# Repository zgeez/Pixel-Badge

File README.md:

# Pixel Badge

A wearable 32 × 32 LED badge that shows a QR code, text and animations, and
hands out a contact link over NFC. A phone app sets it up over Bluetooth.

I designed the PCB in KiCad, wrote the firmware on Zephyr, and built the
Android app in Flutter. The firmware started on an nRF5340 DK with a HUB75
panel and now runs on the custom nRF52840 board.

## Where it stands

Rev A boards are built and working (November 2026). Bring-up turned up an
assembly fault on the module, a scan that flickered, and a few USB and
charging quirks. All are fixed. Board 1 runs everything: display, BLE, NFC,
motion, audio and charging. It lasted 22 hours on the battery showing a QR
code at half brightness.

Bare LEDs make a QR code that phones struggle to read. A printed white diffuser
over the matrix fixes that, so the code scans easily. That's a first hands-on
result, not a formal scan test yet.

Still untested: NFC and BLE range, thermals, and System OFF on the battery.
[Bring-up record](validation/results/2026-11-03-rev-a-bringup/README.md),
[all test records](docs/validation.md).

<p align="center">
  
  <br>
  <em>Tilt-driven particle fluid (click for video).</em>
</p>

## What it does

- Shows a contact QR code and serves the same link from a passive NFC tag.
- Displays text, drawings and grayscale animations of up to 128 frames.
- Rotates with the IMU and runs a particle fluid effect.
- Shows microphone level and spectrum. An opt-in bench build can stream
  encrypted audio to the phone, which stores it. Audio never touches the
  badge's flash.

## Inside

| | |
|---|---|
| MCU | Ebyte E73 module (nRF52840), BLE and app on one core |
| Display | 1024 white LEDs at 2 mm pitch, constant-current column drivers, hardware-timed scan |
| Board | 118 × 76 mm, four layers, all parts on the front |
| Power | USB-C, BQ25620 charger, protected 2500 mAh LiPo, separate LED rail |
| Sensors | ICM-42688-P IMU, PDM microphone, NT3H2111 NFC tag with a PCB coil |
| Firmware | C++17 and C on Zephyr, nRF Connect SDK 3.4.1 |
| App | Flutter, Android |

The CPU doesn't drive the LED scan. SPI DMA, timers and PPI do, and the CPU
takes one interrupt per brightness plane. If the firmware ever stops, a
hardware one-shot blanks the matrix within about a millisecond. Settings
changes over BLE are staged, applied one at a time and read back before the
app shows them as done. [How it fits together](docs/architecture.md).

## Carrier

A 3D-printed carrier holds the board and battery. It clips on with a magnetic
backing or hangs from a lanyard, in portrait or landscape. Print files are in
[hardware/mechanical](hardware/mechanical/).

## Prototype

Before the boards existed, the firmware ran on an nRF5340 DK driving an RGB
HUB75 panel, with breakout boards for the tag, IMU and microphone. That bench
still builds and is useful for app work.

## App

Badge, Links, Text and Studio pages (test data). [App README](app/README.md).

## Build

Install nRF Connect SDK 3.4.1 and its toolchain, then from PowerShell:

```powershell
.\scripts\dev.ps1 build -Image Main -Pristine
.\scripts\dev.ps1 build -Image Prototype -Pristine
.\scripts\dev.ps1 test     # host tests, needs Docker
.\scripts\dev.ps1 check
```

Main ships with the LED output, charging and recording turned off. Bench
add-ons turn them on deliberately. [Firmware guide](docs/firmware.md),
[bring-up checklist](docs/bringup.md).

## Repository

[firmware/](firmware/README.md), [hardware/](hardware/README.md),
[app/](app/README.md), [docs/](docs/README.md),
[design decisions](docs/decisions/README.md).

## License

[MIT](LICENSE), with some [third-party notices and Apache-2.0 board files](docs/firmware.md#licenses).

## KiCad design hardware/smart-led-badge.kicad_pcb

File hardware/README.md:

# Hardware

The KiCad 10.0.6 project for the Rev A badge: a 118 × 76 mm, four-layer board
with every assembled part on the front. Boards are built and running
([bring-up record](../validation/results/2026-11-03-rev-a-bringup/README.md)).

Open `smart-led-badge.kicad_pro`. Project libraries use `${KIPRJMOD}` paths,
and you'll also need KiCad's standard libraries.

| Path | Contents |
|---|---|
| `smart-led-badge.kicad_sch`, `sheets/` | Schematic |
| `smart-led-badge.kicad_pcb` | Routed board |
| `smart-led-badge.kicad_dru` | Custom design rules |
| [libraries/](libraries/README.md) | Symbols, footprints and where they came from |
| `mechanical/` | 3MF print files, below |

## Board

- 1.6 mm, 3 mm corner radius, JLC04161H-7628 stack-up, tented vias.
- Rows route on F.Cu and columns via to In2.Cu. In1.Cu is ground apart from
  three short links.
- 0.127 mm minimum track and space, 0.45/0.2 mm vias. The custom rules allow
  the matrix LEDs' courtyards to touch.
- Keep-outs for the NFC coil, the antenna and the battery. Nothing is
  assembled or exposed under the pack.
- Test points, battery polarity and controls are labelled on silkscreen.
  Reference designators aren't printed.

## Print files

| File | Part |
|---|---|
| `rear-carrier.3mf`, `front-face.3mf` | The two halves of the carrier |
| `matrix-pixel-grid.3mf`, `matrix-diffuser.3mf` | Black 2 mm grid and white diffuser over the matrix |
| `mode-button-cap.3mf`, `action-button-cap.3mf`, `button-plunger.3mf` | Button parts |
| `magnetic-backing.3mf`, `magnet-retaining-cap.3mf` | Magnetic mount |
| `m2-thread-coupon.3mf` | Test print for the M2 threads |
| `pcb-no-rear-jst.3mf` | Board dummy for fit checks (without the rear connector) |

The diffuser is what makes the QR code readable for phones. Fit, latch
retention and wear still need checking on prints.

## Checks

```powershell
.\scripts\dev.ps1 hardware
```

On Linux, `make hardware`. It runs ERC, checks that symbol pin numbers match
footprint pads, and exports PDF and BOM files to `build/hardware/`. It
doesn't check footprint geometry or pin functions, and DRC is separate.
Gerbers, drill, placement and STEP files are generated and kept out of the
repository.

[Hardware overview](../docs/hardware.md), [bring-up checklist](../docs/bringup.md).

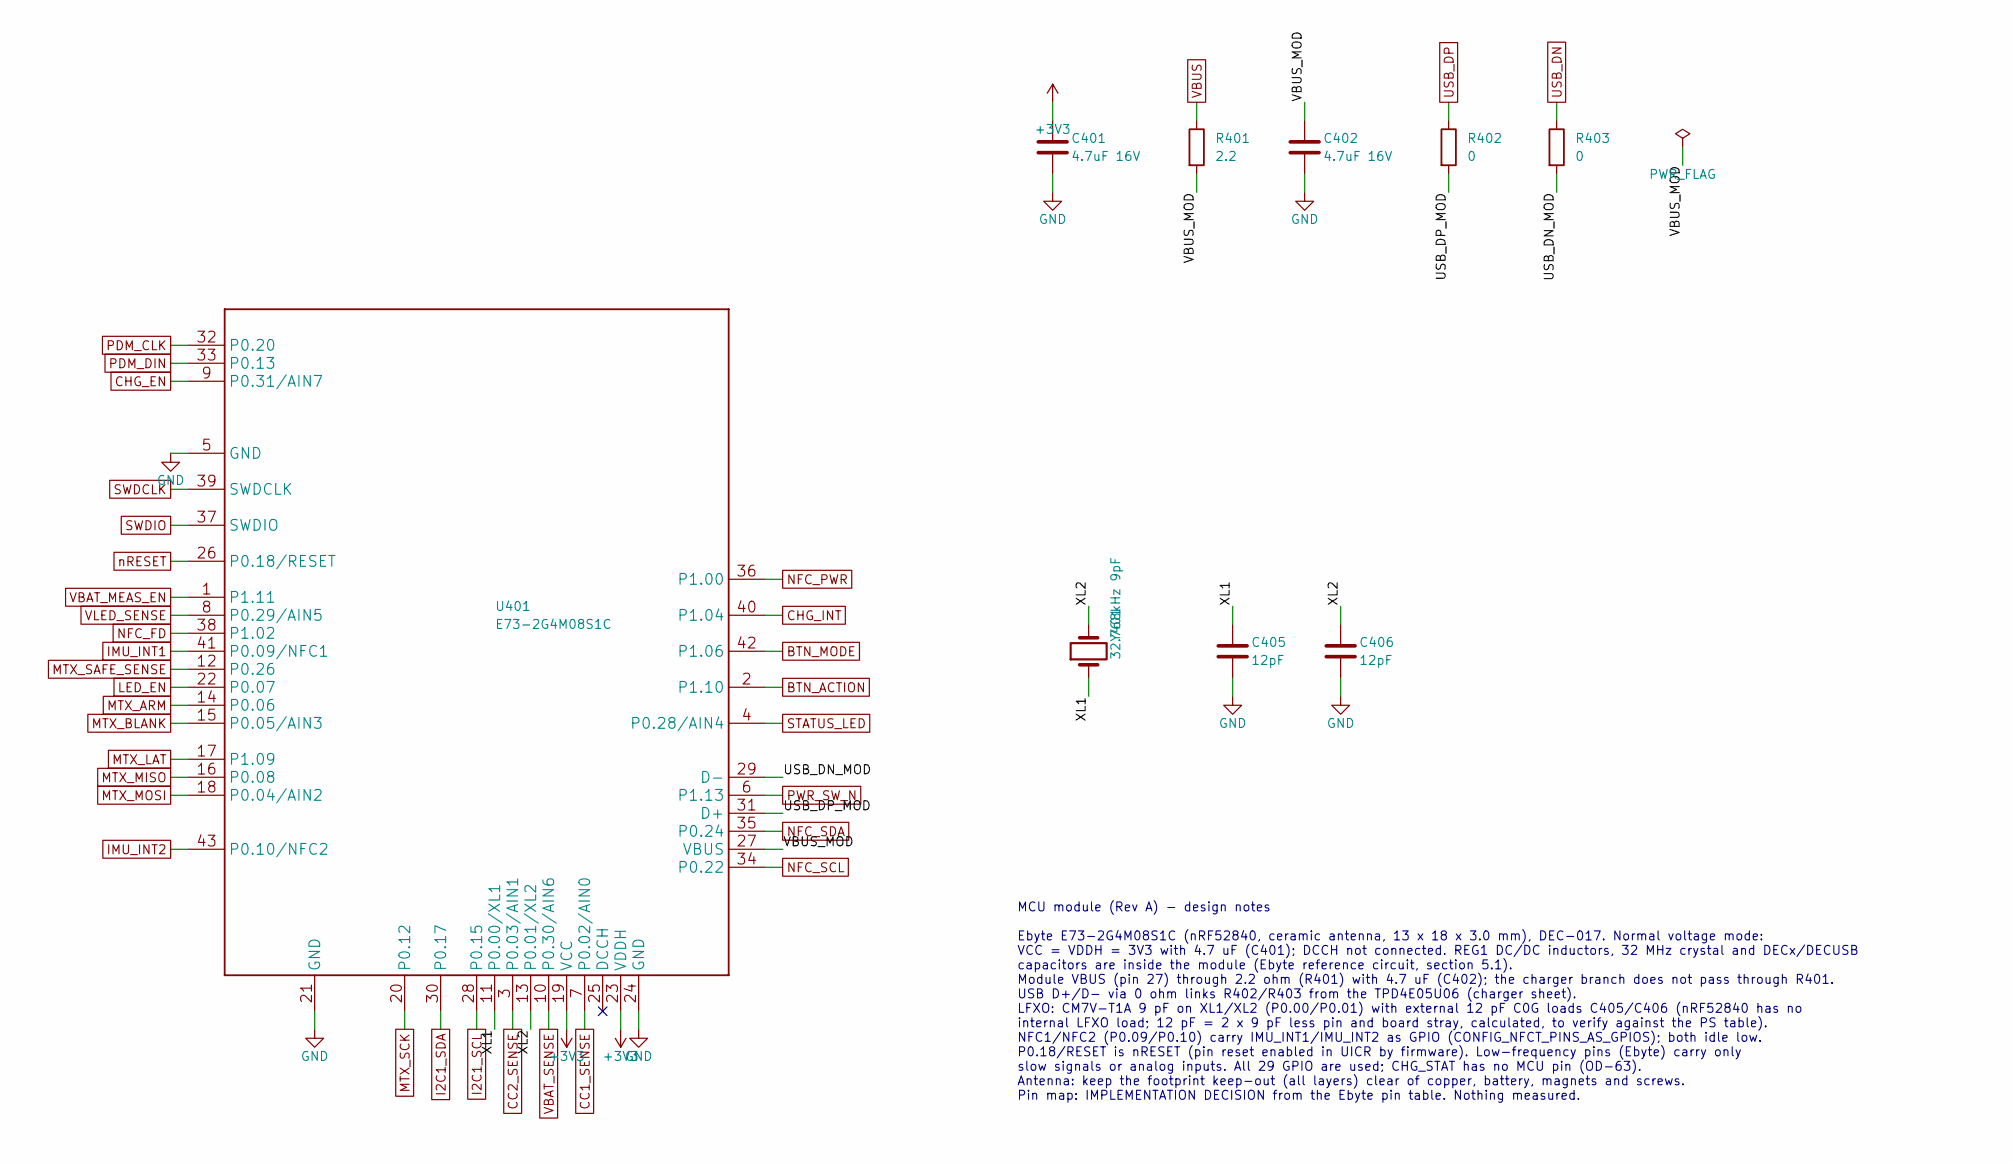
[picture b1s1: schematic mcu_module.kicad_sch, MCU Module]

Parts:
C401, C402: 4.7uF 16V; C_0603_1608Metric; MPN CL10A475KO8NNNC; LCSC C19666
C405, C406: 12pF; C_0402_1005Metric; MPN 0402CG120J500NT; LCSC C1547
R401: 2.2; R_0603_1608Metric; MPN 0603WAF220KT5E; LCSC C22939
R402, R403: 0; R_0402_1005Metric; MPN 0402WGF0000TCE; LCSC C17168
U401: E73-2G4M08S1C; Ebyte_E73-2G4M08S1C; MPN E73-2G4M08S1C; LCSC C356849
Y401: 32.768kHz 9pF; Crystal_SMD_3215-2Pin_3.2x1.5mm; MPN CM7V-T1A-32.768KHZ-9PF-20PPM-TA-QC; LCSC C5366538

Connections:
+3V3: C401.1, U401.19 (VCC), U401.23 (VDDH); also elsewhere on the board
/MCU Module/USB_DN_MOD: R403.2, U401.29 (D-)
/MCU Module/USB_DP_MOD: R402.2, U401.31 (D+)
/MCU Module/VBUS_MOD: C402.1, R401.2, U401.27 (VBUS)
/MCU Module/XL1: C405.1, U401.11 (P0.00/XL1), Y401.1
/MCU Module/XL2: C406.1, U401.13 (P0.01/XL2), Y401.2
BTN_ACTION: U401.2 (P1.10); also elsewhere on the board
BTN_MODE: U401.42 (P1.06); also elsewhere on the board
CC1_SENSE: U401.7 (P0.02/AIN0); also elsewhere on the board
CC2_SENSE: U401.3 (P0.03/AIN1); also elsewhere on the board
CHG_EN: U401.9 (P0.31/AIN7); also elsewhere on the board
CHG_INT: U401.40 (P1.04); also elsewhere on the board
GND: C401.2, C402.2, C405.2, C406.2, U401.5 (GND), U401.21 (GND), U401.24 (GND); also elsewhere on the board
I2C1_SCL: U401.28 (P0.15); also elsewhere on the board
I2C1_SDA: U401.30 (P0.17); also elsewhere on the board
IMU_INT1: U401.41 (P0.09/NFC1); also elsewhere on the board
IMU_INT2: U401.43 (P0.10/NFC2); also elsewhere on the board
LED_EN: U401.22 (P0.07); also elsewhere on the board
MTX_ARM: U401.14 (P0.06); also elsewhere on the board
MTX_BLANK: U401.15 (P0.05/AIN3); also elsewhere on the board
MTX_LAT: U401.17 (P1.09); also elsewhere on the board
MTX_MISO: U401.16 (P0.08); also elsewhere on the board
MTX_MOSI: U401.18 (P0.04/AIN2); also elsewhere on the board
MTX_SAFE_SENSE: U401.12 (P0.26); also elsewhere on the board
MTX_SCK: U401.20 (P0.12); also elsewhere on the board
NFC_FD: U401.38 (P1.02); also elsewhere on the board
NFC_PWR: U401.36 (P1.00); also elsewhere on the board
NFC_SCL: U401.34 (P0.22); also elsewhere on the board
NFC_SDA: U401.35 (P0.24); also elsewhere on the board
PDM_CLK: U401.32 (P0.20); also elsewhere on the board
PDM_DIN: U401.33 (P0.13); also elsewhere on the board
PWR_SW_N: U401.6 (P1.13); also elsewhere on the board
STATUS_LED: U401.4 (P0.28/AIN4); also elsewhere on the board
SWDCLK: U401.39 (SWDCLK); also elsewhere on the board
SWDIO: U401.37 (SWDIO); also elsewhere on the board
USB_DN: R403.1; also elsewhere on the board
USB_DP: R402.1; also elsewhere on the board
VBAT_MEAS_EN: U401.1 (P1.11); also elsewhere on the board
VBAT_SENSE: U401.10 (P0.30/AIN6); also elsewhere on the board
VBUS: R401.1; also elsewhere on the board
VLED_SENSE: U401.8 (P0.29/AIN5); also elsewhere on the board
nRESET: U401.26 (P0.18/RESET); also elsewhere on the board

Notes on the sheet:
MCU module (Rev A) - design notes Ebyte E73-2G4M08S1C (nRF52840, ceramic antenna, 13 x 18 x 3.0 mm), DEC-017. Normal voltage mode: VCC = VDDH = 3V3 with 4.7 uF (C401); DCCH not connected. REG1 DC/DC inductors, 32 MHz crystal and DECx/DECUSB capacitors are inside the module (Ebyte reference circuit,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

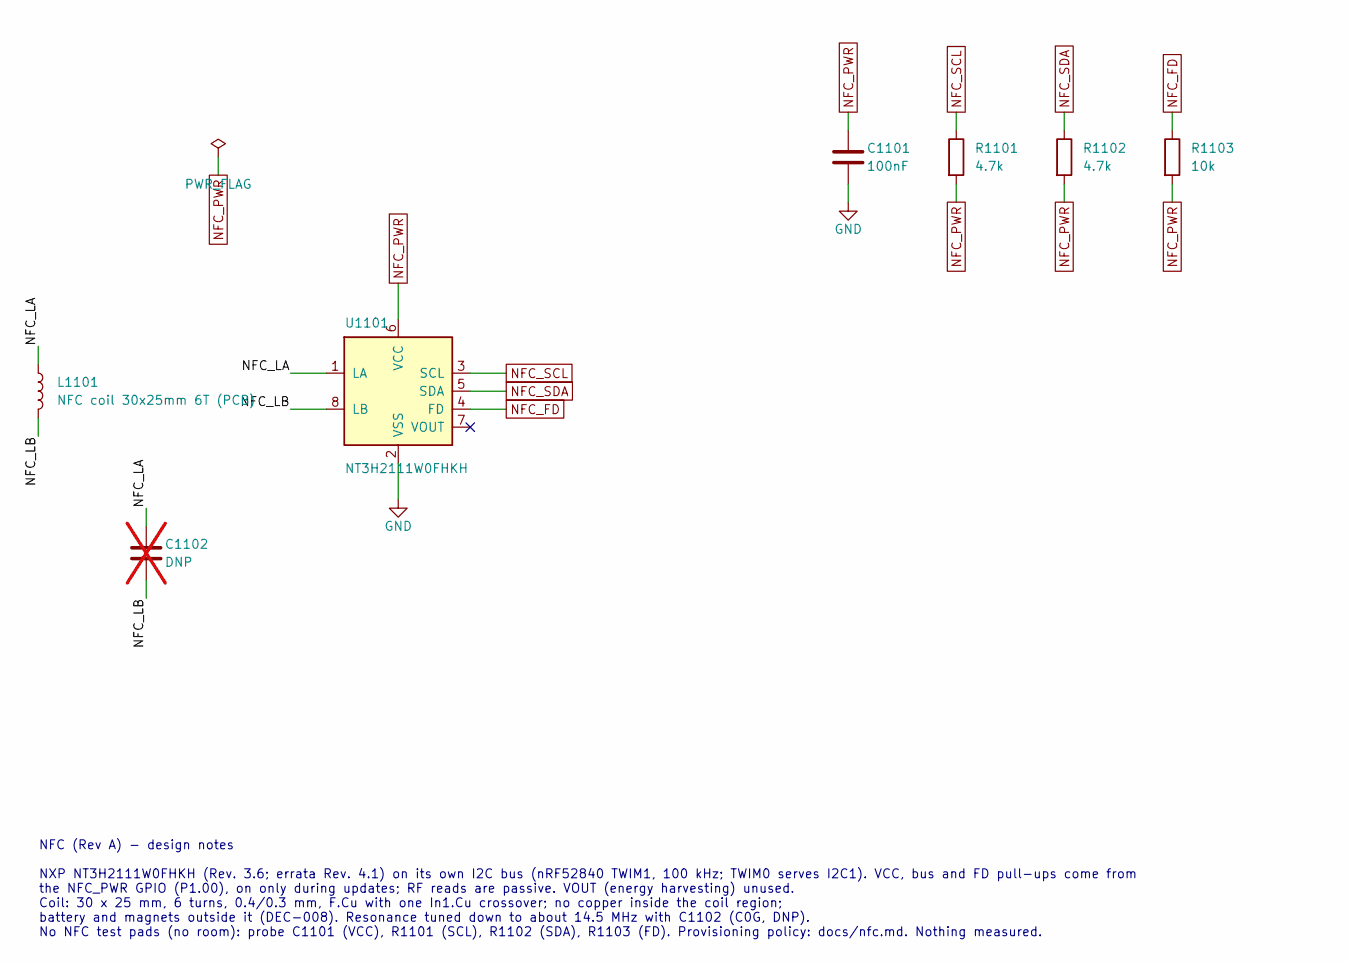
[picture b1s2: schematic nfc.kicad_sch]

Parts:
C1101: 100nF; C_0402_1005Metric; MPN CL05B104KO5NNNC; LCSC C1525
C1102: DNP; C_0402_1005Metric; not fitted
L1101: NFC coil 30x25mm 6T (PCB); L_NFC_Coil_30x25mm_6T
R1101, R1102: 4.7k; R_0402_1005Metric; MPN 0402WGF4701TCE; LCSC C25900
R1103: 10k; R_0402_1005Metric; MPN 0402WGF1002TCE; LCSC C25744
U1101: NT3H2111W0FHKH; NXP_XQFN-8_SOT902-3; MPN NT3H2111W0FHKH; LCSC C710403

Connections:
/NFC/NFC_LA: C1102.1, L1101.1, U1101.1 (LA)
/NFC/NFC_LB: C1102.2, L1101.2, U1101.8 (LB)
GND: C1101.2, U1101.2 (VSS); also elsewhere on the board
NFC_FD: R1103.1, U1101.4 (FD); also elsewhere on the board
NFC_PWR: C1101.1, R1101.2, R1102.2, R1103.2, U1101.6 (VCC); also elsewhere on the board
NFC_SCL: R1101.1, U1101.3 (SCL); also elsewhere on the board
NFC_SDA: R1102.1, U1101.5 (SDA); also elsewhere on the board

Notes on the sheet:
NFC (Rev A) - design notes NXP NT3H2111W0FHKH (Rev. 3.6; errata Rev. 4.1) on its own I2C bus (nRF52840 TWIM1, 100 kHz; TWIM0 serves I2C1). VCC, bus and FD pull-ups come from the NFC_PWR GPIO (P1.00), on only during updates; RF reads are passive. VOUT (energy harvesting) unused. Coil: 30 x 25 mm, 6 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

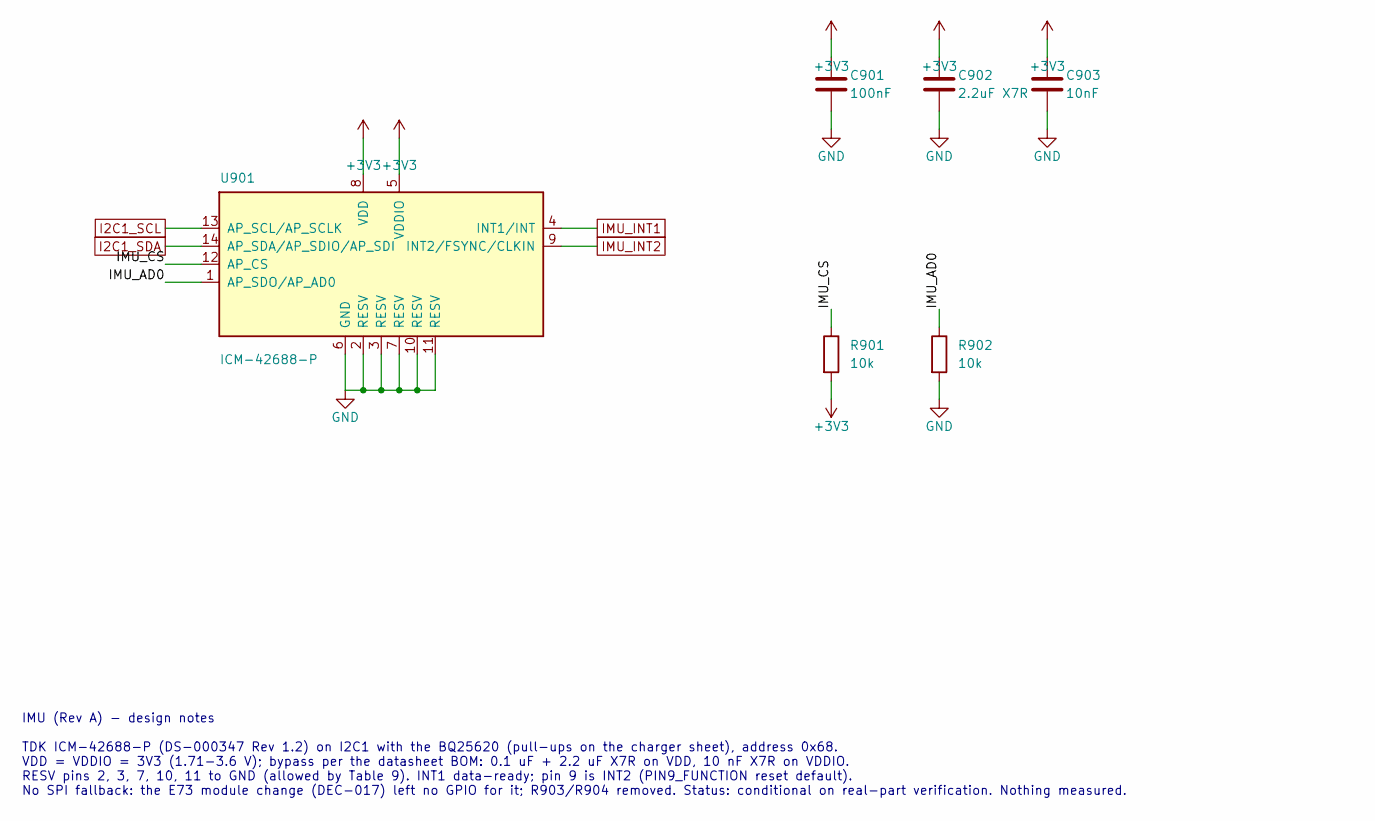
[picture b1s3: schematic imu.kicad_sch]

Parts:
C901: 100nF; C_0402_1005Metric; MPN CL05B104KO5NNNC; LCSC C1525
C902: 2.2uF X7R; C_0603_1608Metric; MPN 0603B225K160NT; LCSC C43922
C903: 10nF; C_0402_1005Metric; MPN CL05B103KB5NNNC; LCSC C15195
R901, R902: 10k; R_0402_1005Metric; MPN 0402WGF1002TCE; LCSC C25744
U901: ICM-42688-P; LGA-14_3x2.5mm_P0.5mm_LayoutBorder3x4y; MPN ICM-42688-P; LCSC C1850418

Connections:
+3V3: C901.1, C902.1, C903.1, R901.2, U901.5 (VDDIO), U901.8 (VDD); also elsewhere on the board
/IMU/IMU_AD0: R902.1, U901.1 (AP_SDO/AP_AD0)
/IMU/IMU_CS: R901.1, U901.12 (AP_CS)
GND: C901.2, C902.2, C903.2, R902.2, U901.2 (RESV), U901.3 (RESV), U901.6 (GND), U901.7 (RESV), U901.10 (RESV), U901.11 (RESV); also elsewhere on the board
I2C1_SCL: U901.13 (AP_SCL/AP_SCLK); also elsewhere on the board
I2C1_SDA: U901.14 (AP_SDA/AP_SDIO/AP_SDI); also elsewhere on the board
IMU_INT1: U901.4 (INT1/INT); also elsewhere on the board
IMU_INT2: U901.9 (INT2/FSYNC/CLKIN); also elsewhere on the board

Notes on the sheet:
IMU (Rev A) - design notes TDK ICM-42688-P (DS-000347 Rev 1.2) on I2C1 with the BQ25620 (pull-ups on the charger sheet), address 0x68. VDD = VDDIO = 3V3 (1.71-3.6 V); bypass per the datasheet BOM: 0.1 uF + 2.2 uF X7R on VDD, 10 nF X7R on VDDIO. RESV pins 2, 3, 7, 10, 11 to GND (allowed by Table 9).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

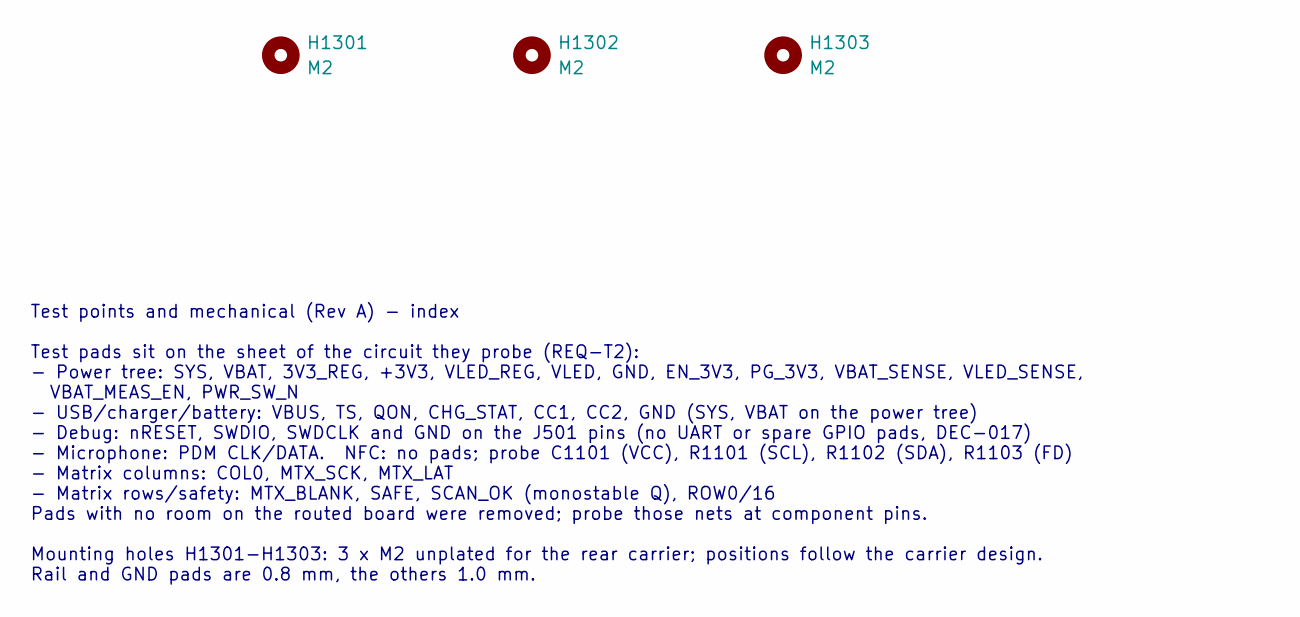
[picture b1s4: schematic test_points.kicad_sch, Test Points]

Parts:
H1301, H1302, H1303: M2; MountingHole_2.2mm_M2

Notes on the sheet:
Test points and mechanical (Rev A) - index Test pads sit on the sheet of the circuit they probe (REQ-T2): - Power tree: SYS, VBAT, 3V3_REG, +3V3, VLED_REG, VLED, GND, EN_3V3, PG_3V3, VBAT_SENSE, VLED_SENSE, VBAT_MEAS_EN, PWR_SW_N - USB/charger/battery: VBUS, TS, QON, CHG_STAT, CC1, CC2, GND (SYS, V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

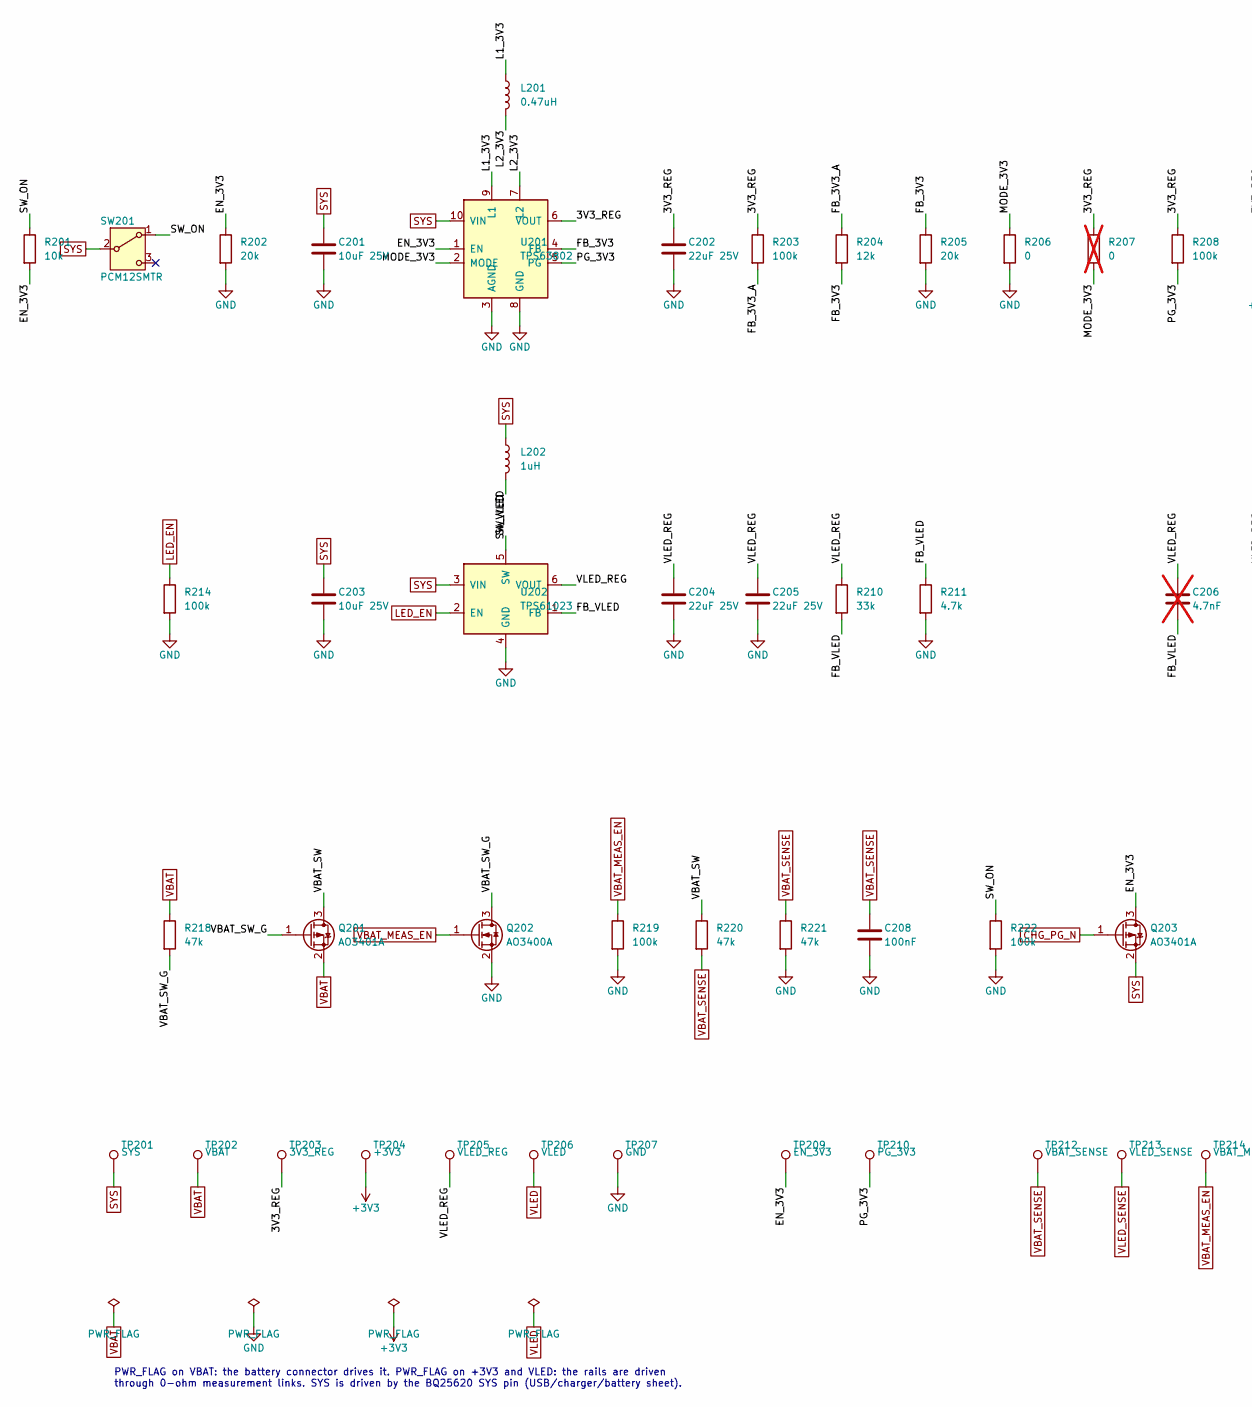
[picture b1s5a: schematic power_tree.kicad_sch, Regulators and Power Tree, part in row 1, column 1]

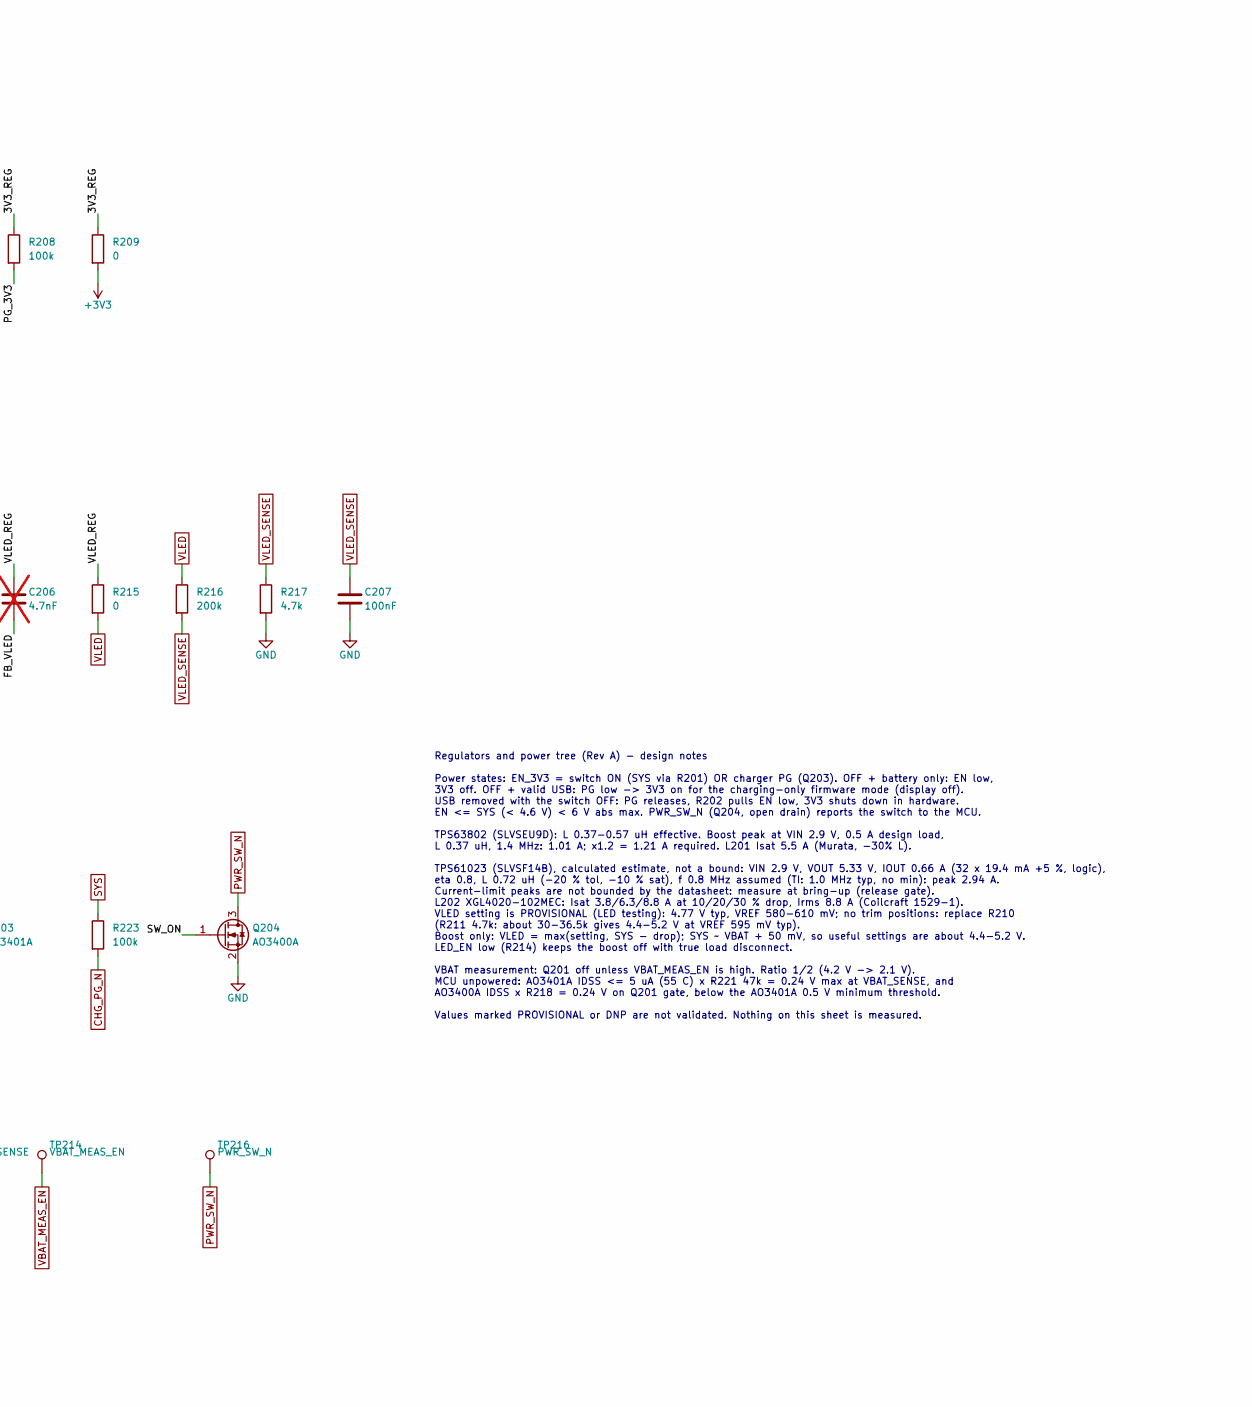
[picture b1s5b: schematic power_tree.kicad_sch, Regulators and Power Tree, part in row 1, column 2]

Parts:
C201, C203: 10uF 25V; C_0805_2012Metric; MPN CL21A106KAYNNNE; LCSC C15850
C202, C204, C205: 22uF 25V; C_0805_2012Metric; MPN CL21A226MAQNNNE; LCSC C45783
C206: 4.7nF; C_0402_1005Metric; not fitted
C207, C208: 100nF; C_0402_1005Metric; MPN CL05B104KO5NNNC; LCSC C1525
L201: 0.47uH; L_Murata_DFE201612E; MPN DFE201612E-R47M=P2; LCSC C668312
L202: 1uH; L_Coilcraft_XGL4020; MPN XGL4020-102MEC; LCSC C5357696
Q201, Q203: AO3401A; SOT-23; MPN AO3401A; LCSC C15127
Q202, Q204: AO3400A; SOT-23; MPN AO3400A; LCSC C20917
R201: 10k; R_0402_1005Metric; MPN 0402WGF1002TCE; LCSC C25744
R202, R205: 20k; R_0402_1005Metric; MPN 0402WGF2002TCE; LCSC C25765
R203, R208, R214, R219, R222, R223: 100k; R_0402_1005Metric; MPN 0402WGF1003TCE; LCSC C25741
R204: 12k; R_0402_1005Metric; MPN 0402WGF1202TCE; LCSC C25752
R206: 0; R_0402_1005Metric; MPN 0402WGF0000TCE; LCSC C17168
R207: 0; R_0402_1005Metric; not fitted
R209, R215: 0; R_0805_2012Metric; MPN 0805W8F0000T5E; LCSC C17477
R210: 33k; R_0402_1005Metric; MPN 0402WGF3302TCE; LCSC C25779
R211, R217: 4.7k; R_0402_1005Metric; MPN 0402WGF4701TCE; LCSC C25900
R216: 200k; R_0402_1005Metric; MPN 0402WGF2003TCE; LCSC C25764
R218, R220, R221: 47k; R_0402_1005Metric; MPN 0402WGF4702TCE; LCSC C25792
SW201: PCM12SMTR; SW_SPDT_PCM12; MPN PCM12SMTR; LCSC C221841
TP201: SYS; TestPoint_Pad_D0.8mm
TP202: VBAT; TestPoint_Pad_D0.8mm
TP203: 3V3_REG; TestPoint_Pad_D0.8mm
TP204: +3V3; TestPoint_Pad_D0.8mm
TP205: VLED_REG; TestPoint_Pad_D0.8mm
TP206: VLED; TestPoint_Pad_D0.8mm
TP207: GND; TestPoint_Pad_D0.8mm
TP209: EN_3V3; TestPoint_Pad_D1.0mm
TP210: PG_3V3; TestPoint_Pad_D1.0mm
TP212: VBAT_SENSE; TestPoint_Pad_D1.0mm
TP213: VLED_SENSE; TestPoint_Pad_D1.0mm
TP214: VBAT_MEAS_EN; TestPoint_Pad_D1.0mm
TP216: PWR_SW_N; TestPoint_Pad_D1.0mm
U201: TPS63802; Texas_DLA0010A; MPN TPS63802DLAR; LCSC C2845237
U202: TPS61023; Texas_DRL0006A; MPN TPS61023DRLR; LCSC C919459

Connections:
+3V3: R209.2, TP204.1; also elsewhere on the board
/Regulators and Power Tree/3V3_REG: C202.1, R203.1, R207.1, R208.1, R209.1, TP203.1, U201.6 (VOUT)
/Regulators and Power Tree/EN_3V3: Q203.3 (D), R201.2, R202.1, TP209.1, U201.1 (EN)
/Regulators and Power Tree/FB_3V3: R204.2, R205.1, U201.4 (FB)
/Regulators and Power Tree/FB_3V3_A: R203.2, R204.1
/Regulators and Power Tree/FB_VLED: C206.2, R210.2, R211.1, U202.1 (FB)
/Regulators and Power Tree/L1_3V3: L201.1, U201.9 (L1)
/Regulators and Power Tree/L2_3V3: L201.2, U201.7 (L2)
/Regulators and Power Tree/MODE_3V3: R206.1, R207.2, U201.2 (MODE)
/Regulators and Power Tree/PG_3V3: R208.2, TP210.1, U201.5 (PG)
/Regulators and Power Tree/SW_ON: Q204.1 (G), R201.1, R222.1, SW201.1 (A)
/Regulators and Power Tree/SW_VLED: L202.2, U202.5 (SW)
/Regulators and Power Tree/VBAT_SW: Q201.3 (D), R220.1
/Regulators and Power Tree/VBAT_SW_G: Q201.1 (G), Q202.3 (D), R218.2
/Regulators and Power Tree/VLED_REG: C204.1, C205.1, C206.1, R210.1, R215.1, TP205.1, U202.6 (VOUT)
CHG_PG_N: Q203.1 (G), R223.2; also elsewhere on the board
GND: C201.2, C202.2, C203.2, C204.2, C205.2, C207.2, C208.2, Q202.2 (S), Q204.2 (S), R202.2, R205.2, R206.2, R211.2, R214.2, R217.2, R219.2, R221.2, R222.2, TP207.1, U201.3 (AGND), U201.8 (GND), U202.4 (GND); also elsewhere on the board
LED_EN: R214.1, U202.2 (EN); also elsewhere on the board
PWR_SW_N: Q204.3 (D), TP216.1; also elsewhere on the board
SYS: C201.1, C203.1, L202.1, Q203.2 (S), R223.1, SW201.2 (B), TP201.1, U201.10 (VIN), U202.3 (VIN); also elsewhere on the board
VBAT: Q201.2 (S), R218.1, TP202.1; also elsewhere on the board
VBAT_MEAS_EN: Q202.1 (G), R219.1, TP214.1; also elsewhere on the board
VBAT_SENSE: C208.1, R220.2, R221.1, TP212.1; also elsewhere on the board
VLED: R215.2, R216.1, TP206.1; also elsewhere on the board
VLED_SENSE: C207.1, R216.2, R217.1, TP213.1; also elsewhere on the board

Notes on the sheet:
PWR_FLAG on VBAT: the battery connector drives it. PWR_FLAG on +3V3 and VLED: the rails are driven through 0-ohm measurement links. SYS is driven by the BQ25620 SYS pin (USB/charger/battery sheet).
Regulators and power tree (Rev A) - design notes Power states: EN_3V3 = switch ON (SYS via R201) OR charger PG (Q203). OFF + battery only: EN low, 3V3 off. OFF + valid USB: PG low -> 3V3 on for the charging-only firmware mode (display off). USB removed with the switch OFF: PG releases, R202 pulls E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

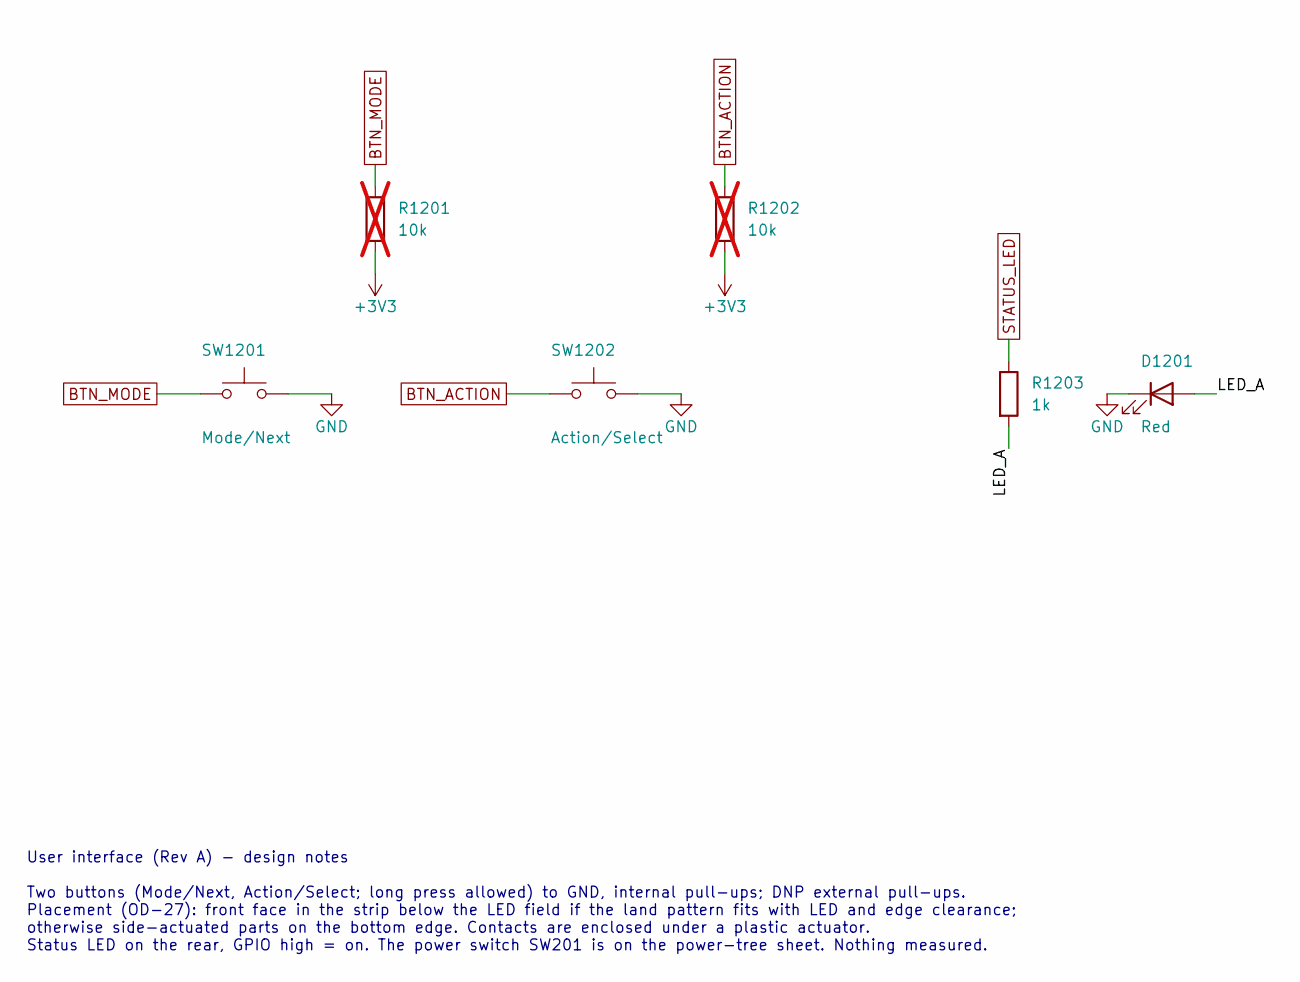
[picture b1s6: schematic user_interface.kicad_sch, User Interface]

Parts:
D1201: Red; LED_0603_1608Metric; MPN KT-0603R; LCSC C2286
R1201, R1202: 10k; R_0402_1005Metric; not fitted
R1203: 1k; R_0402_1005Metric; MPN 0402WGF1001TCE; LCSC C11702
SW1201: Mode/Next; SW_XUNPU_TS-1088; MPN TS-1088-AR02016; LCSC C720477
SW1202: Action/Select; SW_XUNPU_TS-1088; MPN TS-1088-AR02016; LCSC C720477

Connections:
+3V3: R1201.2, R1202.2; also elsewhere on the board
/User Interface/LED_A: D1201.2 (A), R1203.2
BTN_ACTION: R1202.1, SW1202.1; also elsewhere on the board
BTN_MODE: R1201.1, SW1201.1; also elsewhere on the board
GND: D1201.1 (K), SW1201.2, SW1202.2; also elsewhere on the board
STATUS_LED: R1203.1; also elsewhere on the board

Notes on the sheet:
User interface (Rev A) - design notes Two buttons (Mode/Next, Action/Select; long press allowed) to GND, internal pull-ups; DNP external pull-ups. Placement (OD-27): front face in the strip below the LED field if the land pattern fits with LED and edge clearance; otherwise side-actuated parts on th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
